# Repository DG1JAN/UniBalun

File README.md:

# UniBalun
a PCB for a lightweight qrp (maximum 10W SSB & CW or 5W on FT8) 1:49 UnUn (also 1:9,1:64,... possible) or Balun (1:1, 1:4)

Update to Rev. 1.2 with some minor changes (bigger Pads for the Capaciator and updated labeling)

German speaking Hams will now find a new PDF with build instructions (Bauanleitung) in the repo: https://github.com/DG1JAN/UniBalun/blob/main/Bauanleitung_UniBalun.pdf

Depending on the winding of the toroid, you can use the PCB to create a 1:1 or 1:4 Balun or a 1:49 UnUn.

1:1 Balun: solder a wire jumper between Pad 1 and 3. No capacitor.

1:4 Balun: solder a wire jumper between Pad 1 and 2 and another jumper between Pad 3 and 4. No capacitor.

1:49 Unun: solder a wire-jumper between Pad 1 and 4 on the backside of the PCB (gives better isolation). Solder the capaciator to C1

1:9 Unun: solder a wire-jumper between Pad 1 and 4 on the backside of the PCB (gives better isolation). Solder a Wire on the backside of the PCB between the a' Pad and the GND of the BNC-Plug.

I recommend using "Amidon FT82-43" or "Fair-Rite 5943000601" (100% identical to the Amidon) Cores or the "Würth 74270118" core. The Würth core is a bit better on higer Bands, but should not be used below ~6MHz.

PRO-TIP: For lowest losses, use a FT82-43 with a FT50-43 placed inside the FT82. (they fit nicely together) A Fair-Rite 5943000601 & 5943001101 have even a better match!

Measurements have shown that the best winding radio for 1:49 UnUns on the small FT82-43 sized core is 3-to-21. 

The new revision (>1.1) has a combined footprint for BNC and SMA connectors, so only one version of the PCB is needed (thanks to DL2MAN for the idea).
For BNC connection you can use the Part: Amphenol B6252H7 / Telegärtner J01001A0038 (or similar) <br>
For SMA connection pls use a straight edge mount SMA connector (found some cheap sources at amazon, e.g. : https://www.amazon.de/10-polig-SMA-Buchse-Leiterplattenmontage-Adapter-HF-Steckverbinder-Messing/dp/B07QG2Y9L6/ref=sr_1_3?keywords=sma+buchse&qid=1662800069&sr=8-3 )

I add two new PADs in revision 1.1 to solder 4mm ("Bana Connector") sockets directly to the PCB. I used this parts: https://www.amazon.de/gp/product/B07VYSN74H/ref=ppx_yo_dt_b_asin_title_o01_s00?ie=UTF8&th=1 

For German or EU-based OM's, I can recommend https://aisler.net/ for PCB manufacturing. You can upload the Kicad file and order the PCBs.<br>
I also have good experience with http://JLCPCB.com from China. You can upload the Gerber Files (as Zip-File) directly to their homepage. delivery time to Germany is ~10 to 14 days.
Manuel (DL2MAN) did a short How-To-Order here on Youtube: https://www.youtube.com/watch?v=1b3oLp7s9gk&t=5s

Pictures from a  1:49 UnUn build:

Pictures from a  1:9 UnUn build:

Here are some YouTube Videos related to the Project:

https://youtu.be/JOxsU2A5xWw?si=09692yh69wdoD_nu

https://youtu.be/WJNUpXuDDTQ?si=r2ZIQGWQCxN_N85m

https://youtu.be/oUK1LmV6amc?si=wLx39TDfT2uAble6

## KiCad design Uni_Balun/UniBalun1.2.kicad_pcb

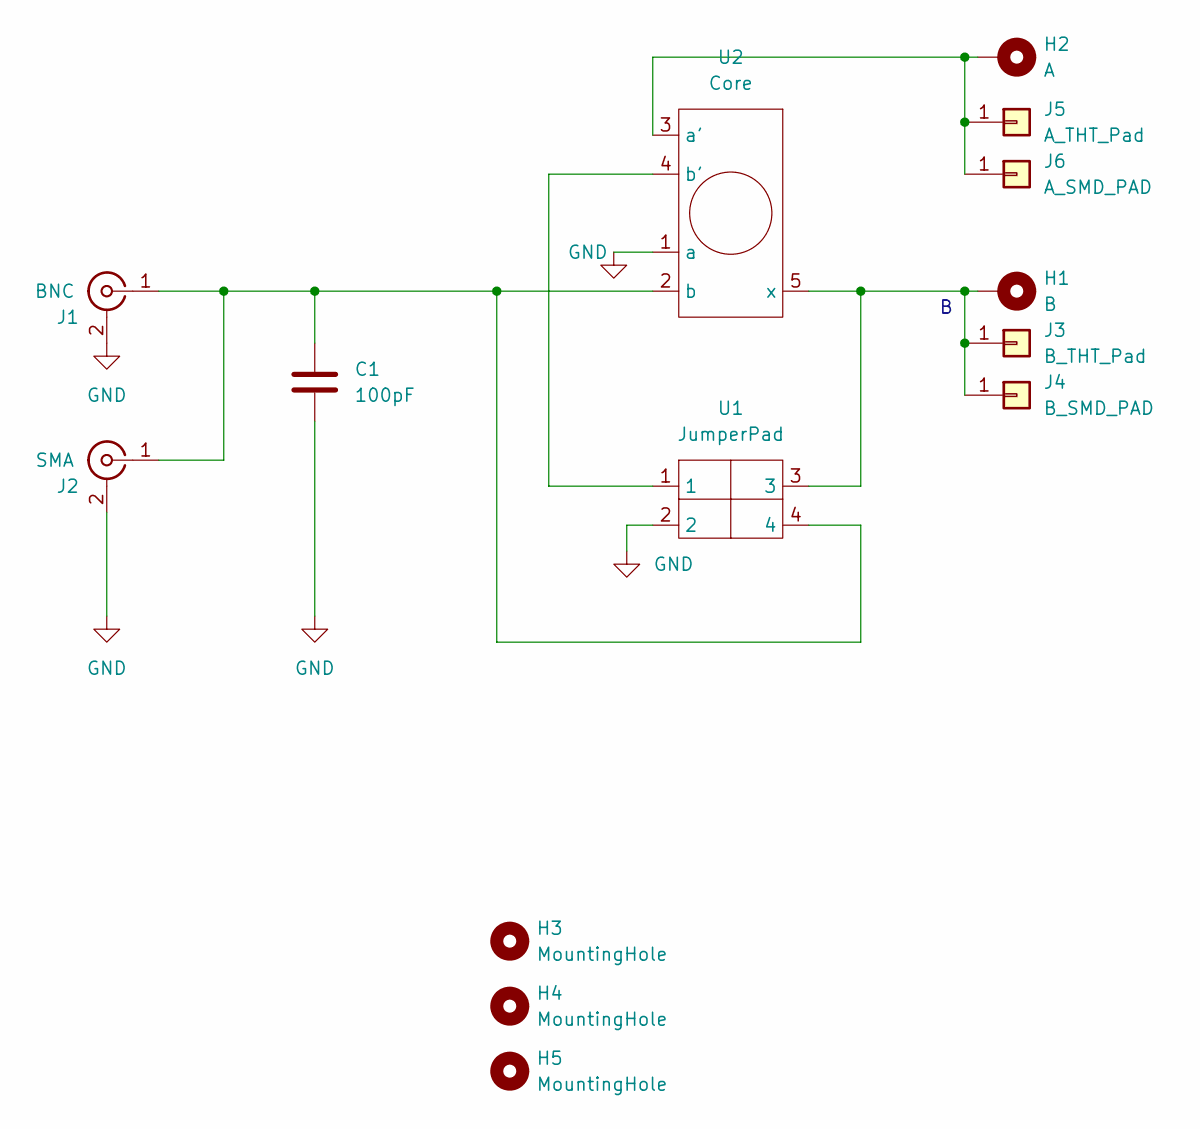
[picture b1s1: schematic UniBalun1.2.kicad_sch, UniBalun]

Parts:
C1: 100pF; THT_cap
H1: B; MountingHole_3.2mm_M3_Pad
H2: A; MountingHole_3.2mm_M3_Pad
H3, H4: MountingHole; MountingHole_2.1mm
H5: MountingHole; MountingHole_4.5mm
J1: BNC; BNC_Amphenol_B6252HB-NPP3G-50_Horizontal
J2: SMA; SMA_Samtec_SMA-J-P-X-ST-EM1_EdgeMount
J3: B_THT_Pad; SolderWire-1.5sqmm_1x01_D1.7mm_OD3.9mm
J4: B_SMD_PAD; 4mmJack
J5: A_THT_Pad; SolderWire-1.5sqmm_1x01_D1.7mm_OD3.9mm
J6: A_SMD_PAD; 4mmJack
U1: JumperPad; Jumper
U2: Core; FT82_Balun

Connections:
GND: C1.2, J1.2 (Ext), J2.2 (Ext), U1.2, U2.1 (a)
unnamed: C1.1, J1.1 (In), J2.1 (In), U1.4, U2.2 (b)
unnamed: H1.1, J3.1, J4.1, U1.3, U2.5 (x)
unnamed: H2.1, J5.1, J6.1, U2.3 (a')
unnamed: U1.1, U2.4 (b')

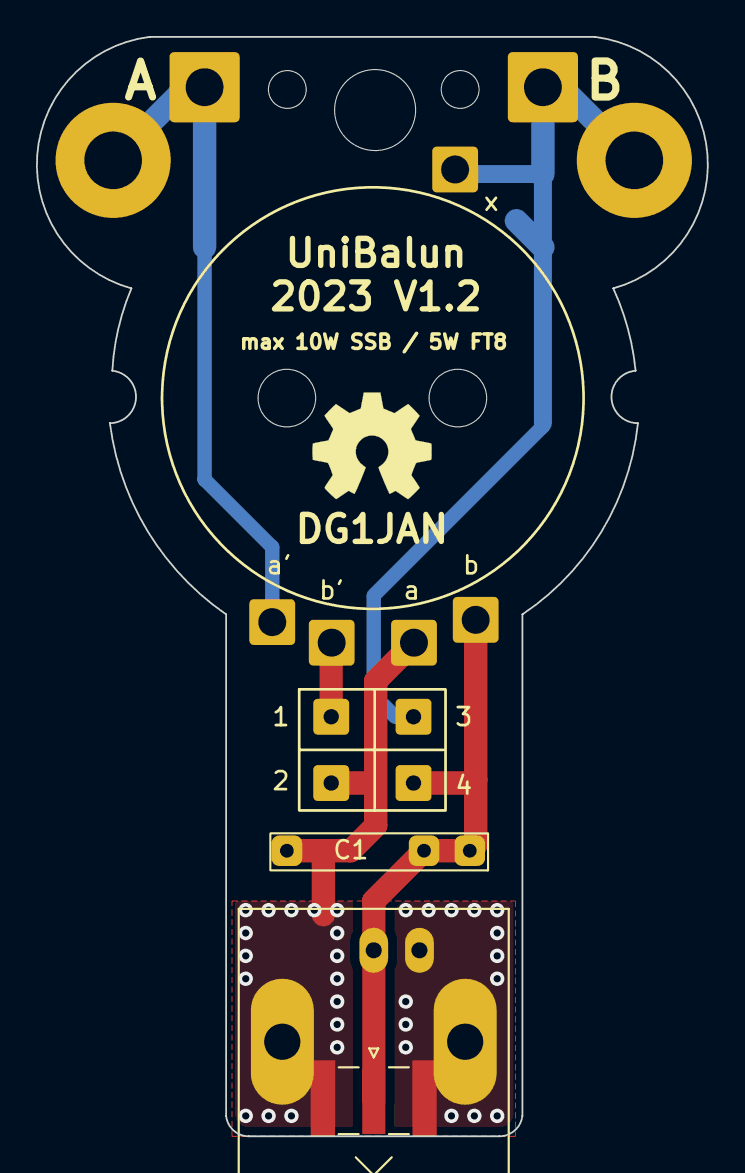
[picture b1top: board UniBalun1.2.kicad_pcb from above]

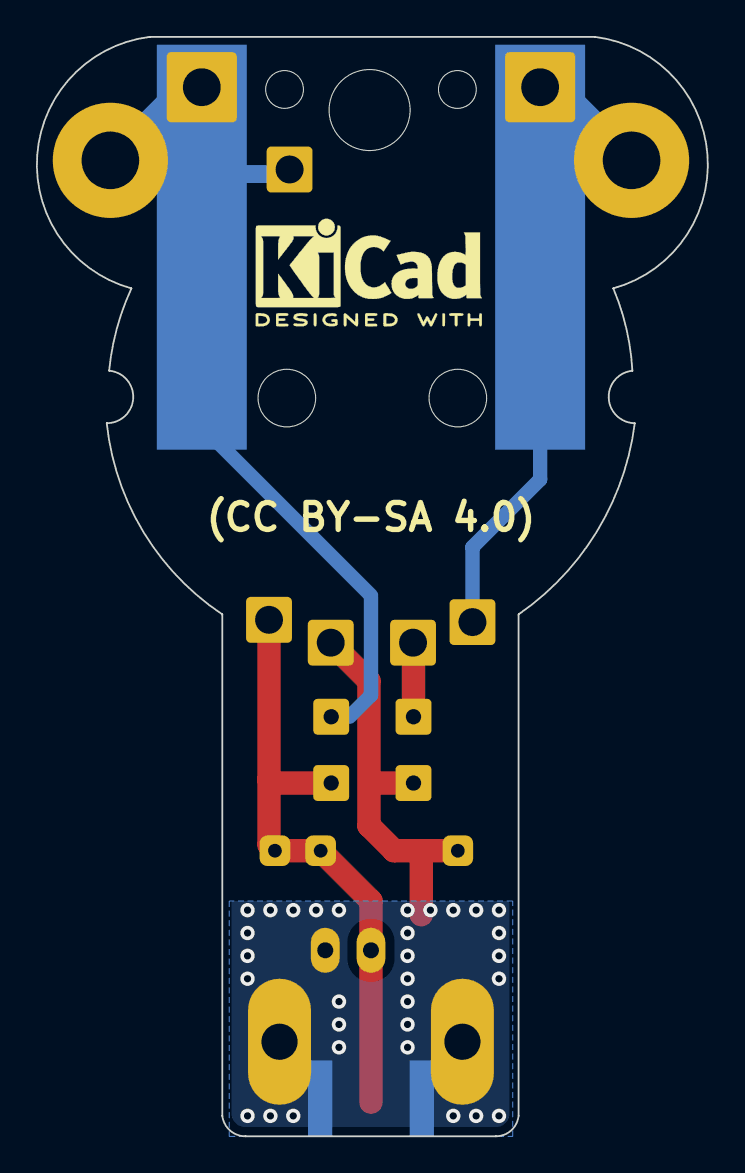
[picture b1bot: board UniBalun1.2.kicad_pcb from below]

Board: 2 copper layers, 37.3 x 61.1 mm, 14 parts (2 on the bottom side), 5 nets.

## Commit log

2022-07-14 Alternativ Version using a BNC instead of SMA
2022-07-14 fixed typo
2022-09-09 update new layout
    update for new version of Layout
2022-09-21 update picture
2023-02-03 update to Rev 1.2
    only smal changes
    - bigger Pads for the Capaciator
    - updatetd labeling
2023-02-03 upload gerber files for Rev 1.2
2023-02-03 add variants of the UniBalun
    CoaxBalun can be use to Build a 1:1 without need for a (Heav) connector
    UnUn_BNC is a Version only for Endfed Antennas and does only support BNC
2023-02-03 fixed issue with netlist (no functional change, only to prevent DRC Error at Aisler.net)
2023-07-20 Update with 1:9
2023-08-31 clean up
2024-07-15 copy library from v1.1 to current v1.2

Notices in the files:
Uni_Balun/UniBalun1.2.kicad_pcb:
(CC BY-SA 4.0)
